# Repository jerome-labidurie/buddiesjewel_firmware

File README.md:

buddiesjewel_firmware
=====================

Firmware (arduino, attiny45) for BuddiesJewel project

http://fablab-lannion.org/wiki/index.php?title=BuddiesJewel

* attiny45/ : firmware attiny45 et RF430CL330H
* BlinkM/ : archive de BlinkM et outils de flashage
* hardware/ : schémas
* serial2rgb/ : commande d'une led rgb par liason série (via arduino)
* tag2rgb/ : lecture couleur dans un tag et commande rgb (shield nfc reader)
* TI_dynamic_tag/ : utilisation par un arduino du RF430Cl330H

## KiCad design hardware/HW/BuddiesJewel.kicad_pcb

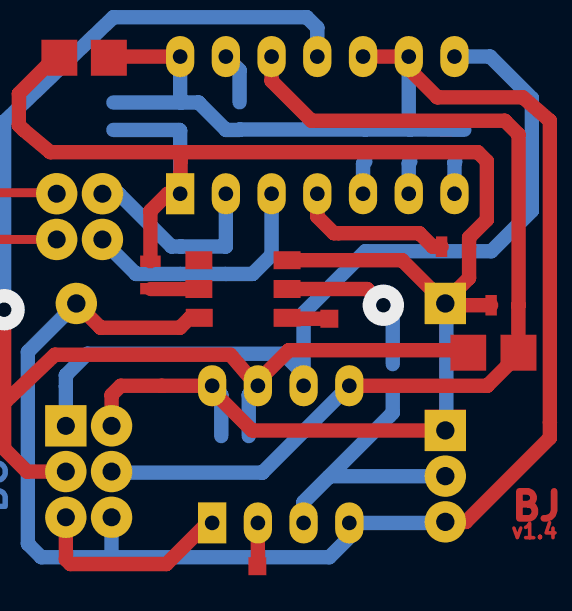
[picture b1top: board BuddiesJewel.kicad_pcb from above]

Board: 2 copper layers, 26 parts (0 on the bottom side), 19 nets.

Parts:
C1: 1 µF; SM0603_Capa
C2: 0,1 µF; SM0603_Capa
C3: 0,47 µF; SM0603_Capa
C4: 22 pF; SM0603_Capa
C5: not equipped; SM0603_Capa
CON1: AVR-ISP6; pin_array_3x2
CON2: ANTENNE; PIN_ARRAY_2X2
CON3: EXT_LED; PIN_ARRAY_3X1
P1: ALIM; Alim
PT1, PT2, PT3, PT4, PT5, PT6: PT; TEST_POINT_1mm
R1, R2, R3: not equipped; SM0603_Resistor
R4, R5, R6, R8: zero R; SM0603_Resistor
R7: 100R; SM0603_Resistor
U1: ATTINY25-P; DIP-8__300_ELL
U2: RF430CL330H; DIP-14__300_ELL
U3: WS2812

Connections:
+3.3V: C1.2, C2.2, CON1.2, CON3.1, P1.1, PT1.1, R1.1, R2.1, R3.2, R7.1, U1.8, U2.1, U3.3
/ANT1: C4.1, C5.1, CON2.1, U2.2
/ANT2: C4.2, C5.2, CON2.2, U2.3
/IT/MISO: CON1.1, U1.6, U2.8
/LED_DI: CON3.2, R8.1, U1.3
/RST: CON1.5, U1.1
/SCL/SCK: CON1.3, PT3.1, R1.2, U1.7, U2.11
/SDA/MOSI: CON1.4, PT4.1, R2.2, U1.5, U2.12
GND: C1.1, C2.1, C3.1, CON1.6, CON3.3, P1.2, PT2.1, R4.2, R5.2, R6.2, U1.4, U2.9, U2.10, U2.14, U3.6
unnamed: R5.1, U2.6
unnamed: R3.1, U2.4
unnamed: R6.1, U2.7
unnamed: R4.1, U2.5
unnamed: R8.2, U3.2
unnamed: PT5.1, U3.1
unnamed: PT6.1, U1.2
unnamed: C3.2, U2.13
unnamed: CON2.3, CON2.4
unnamed: R7.2, U3.5

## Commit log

2013-04-05 1st import
2013-04-05 tag2rgb scheme
2013-07-10 add files for BlinkM
2013-07-10 Add hardware - new version for tag2rgb - blinkm connection with arduino
2013-07-10 correct fuse to be modified !
2013-10-02 arduino+RF430
2013-10-02 arduino+RF430 bis
2013-10-26 1ere version attiny45+RF430Cl330H
2013-10-26 commentaires/nettoyage code
2013-11-03 Add hardware pictures
2013-11-05 Write 16 bits registers !
2013-11-07 Adafruit NeoPixel lib original files
2013-11-15 Add kicad hardware scheme
2013-11-18 change "RGB_LED (4)" D2 connector to "EXT_LED (3)" change ATtiny/RF430/WS2812/CON1 connections
2013-11-19 new antenna and some enhanced stuff
2013-11-20 new PCB revision
2013-11-29 BJ_PCB 1.2
    - change track width to class 2 (from .254mm to .5mm), except next to the RF430
    - rearrange component locations
    - add R,C stuff close to the LED WS2812 (NeoPixel) as it is on the little adaFruit NeoPixel board
2013-11-29 (minor) just move PCB .25mm to the right
2013-11-29 add svg generated files for PCB_1.2
2013-11-29 pcb modif following svg file generation
2013-12-01 Use DIP footprint for TI chip Reroute to use 0,5mm nets
2013-12-02 (minor) modif on pcb
2013-12-02 PCB_v1.3
    - fix some bugs (missed connection, bad nodes...)
    - remove some useless vias
    - redo the antenna (just in case where that could work ;)
2013-12-02 PCB_v1.3.1
    (minor) move C2 to the good position
2013-12-03 PCB_v1.4
    **will be used for our first etch**
    - increase track width to .8mm (antenna tracks still in .5mm)
    - remove the LED_DI jumper then replaced with a 0 ohm resistor (freed space)
2013-12-04 attiny45 as arduino
2013-12-04 add extern "C"
2013-12-05 neoPixel + RF430CL330H
2013-12-05 read color from RF430 and send it to neoPixel
2013-12-05 Save read color in EEPROM
2013-12-09 Blink with RF430 version
2013-12-09 Add datasheets
2013-12-09 Add another url for attiny arduino core
2013-12-10 Use interrupts to get tag color when written
2013-12-12 Enable power down mode
2013-12-12 Slowly goes to designated color
2013-12-14 Code cleanup
2013-12-14 A bit more power reduction
2013-12-15 blue blink for version
2013-12-17 Add (a bit) better NDEF parse
2014-01-28 add "rainbow3" for user demo testbench
2014-01-29 - tuning speed of the rainbow - clean source code
